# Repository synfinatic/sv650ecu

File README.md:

## Suzuki SV650 ECU Decoder

This is the Arduino code (for a [PJRC Teensy 2.0](http://www.pjrc.com/store/teensy.html)) 
and necessary CAD/schematic files for creating a PCB to creating your own 
2nd Generation SV650 ECU Decoder to replace the error lights & codes normally 
displayed by the stock dash unit.

This supports the following:

 * Oil pressure warning light
 * Neutral light
 * EFI warning light
 * Low fuel light *
 * Display the water temp from the the stock water temp sensor
 * Ability to decode EFI error codes from the SV650 ECU
 * TPS adjustment indicator **

[*] Note: Untested.

[**] Note: Normally the 4 digit LED display shows the water temp. 
To show the TPS indicator or ECU error codes, you’ll need to use a 
“Suzuki diagnostic tool” (aka a paperclip) to short two wires per the shop manual.

More information about this project is available 
[on my blog](http://synfin.net/sv650ecu "Suzuki SV650 ECU Decoder") and 
[on the wiki](https://github.com/synfinatic/sv650ecu/wiki).

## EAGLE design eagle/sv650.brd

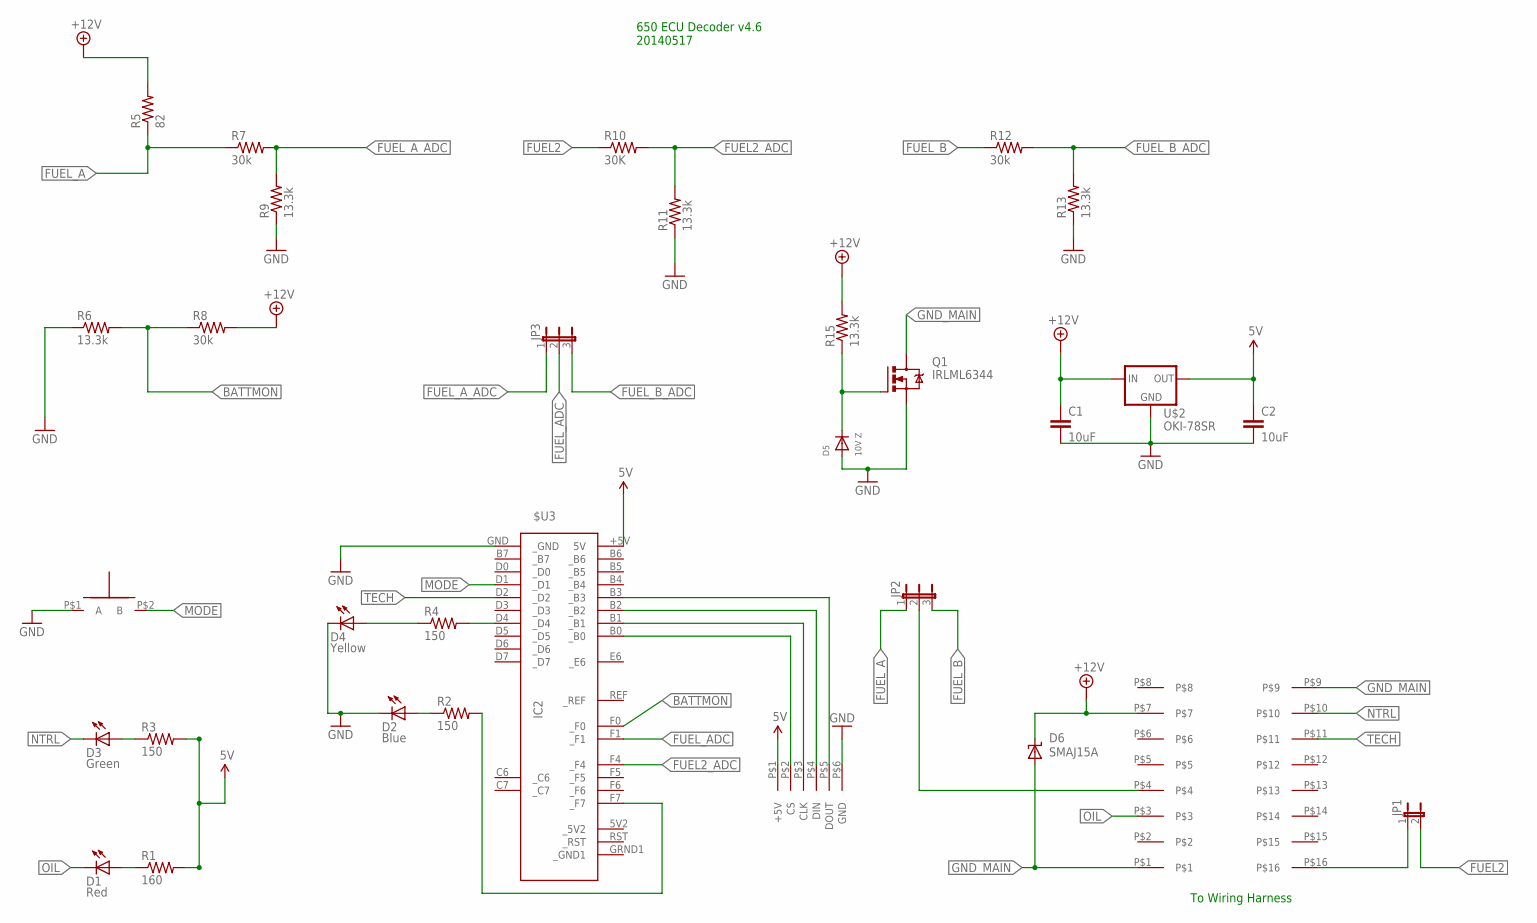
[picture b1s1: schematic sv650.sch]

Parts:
$U3: IC2; TEENSY
C1, C2: 10uF; C0805
D1: Red; LED10MM
D2: Blue; LED5MM
D3: Green; LED10MM
D4: Yellow; LED10MM
D5: 10V Z; SOD-123
D6: SMAJ15A; SMBG
JP1: JP1E; JP1
JP2, JP3: JP2E; JP2
Q1: IRLML6344; SOT23
R1: 160; M0805; MPN CRCW0805160RFKEA
R2, R3, R4: 150; M0805; MPN MCHP05W4F1500T5E
R5: 82; AXIAL-0.9
R6: 13.3k; M0805; MPN CRCW080510K0FKTA
R7, R12: 30k; M0805
R8: 30k; M0805; MPN CRCW080510K0FKTA
R9, R11, R13, R15: 13.3k; M0805
R10: 30K; M0805
U$1: OASIS-7-SEG-DISPLAY
U$2: OKI-78SR; OKI-78SR-H
U$3: TE-174975-2
U$10: R13-509A-05-BB/R13-509A-05-BR

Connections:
5V: $U3.+5V (5V), C2.1, R1.2, R3.2, U$1.P$1 (+5V), U$2.P$3 (OUT)
+12V: C1.1, D6.C, R5.P$2 (2), R8.2, R15.2, U$2.P$1 (IN), U$3.P$7
BATTMON: $U3.F0 (_F0), R6.2, R8.1
FUEL2: JP1.2, R10.1
FUEL2_ADC: $U3.F4 (_F4), R10.2, R11.2
FUEL_A: JP2.1, R5.P$1 (1), R7.1
FUEL_ADC: $U3.F1 (_F1), JP3.2
FUEL_A_ADC: JP3.1, R7.2, R9.2
FUEL_B: JP2.3, R12.1
FUEL_B_ADC: JP3.3, R12.2, R13.2
GND: $U3.GND (_GND), C1.2, C2.2, D2.K (C), D4.K (C), D5.A, Q1.2 (S), R6.1, R9.1, R11.1, R13.1, U$1.P$6 (GND), U$2.P$2 (GND), U$10.P$1 (A)
GND_MAIN: D6.A, Q1.3 (D), U$3.P$1, U$3.P$9
MODE: $U3.D1 (_D1), U$10.P$2 (B)
unnamed: $U3.B0 (_B0), U$1.P$2 (CS)
unnamed: $U3.B1 (_B1), U$1.P$3 (CLK)
unnamed: $U3.B2 (_B2), U$1.P$4 (DIN)
unnamed: $U3.B3 (_B3), U$1.P$5 (DOUT)
unnamed: D3.A, R3.1
unnamed: D2.A, R2.1
unnamed: D1.A, R1.1
unnamed: $U3.D4 (_D4), R4.2
unnamed: JP2.2, U$3.P$4
unnamed: JP1.1, U$3.P$16
unnamed: $U3.F7 (_F7), R2.2
unnamed: D5.C, Q1.1 (G), R15.1
NTRL: D3.K (C), U$3.P$10
OIL: D1.K (C), U$3.P$3
R2: D4.A, R4.1
TECH: $U3.D2 (_D2), U$3.P$11

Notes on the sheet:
To Wiring Harness
650 ECU Decoder v4.6 20140517

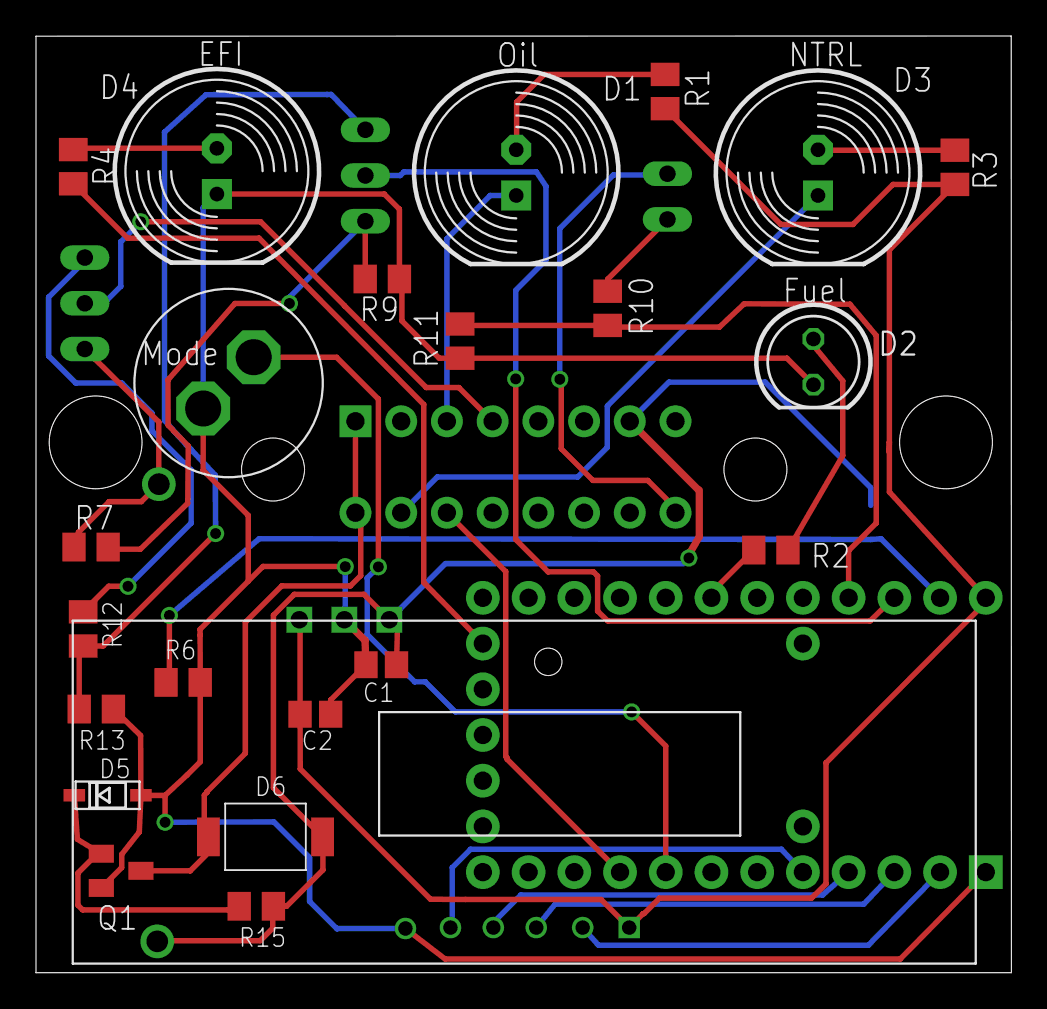
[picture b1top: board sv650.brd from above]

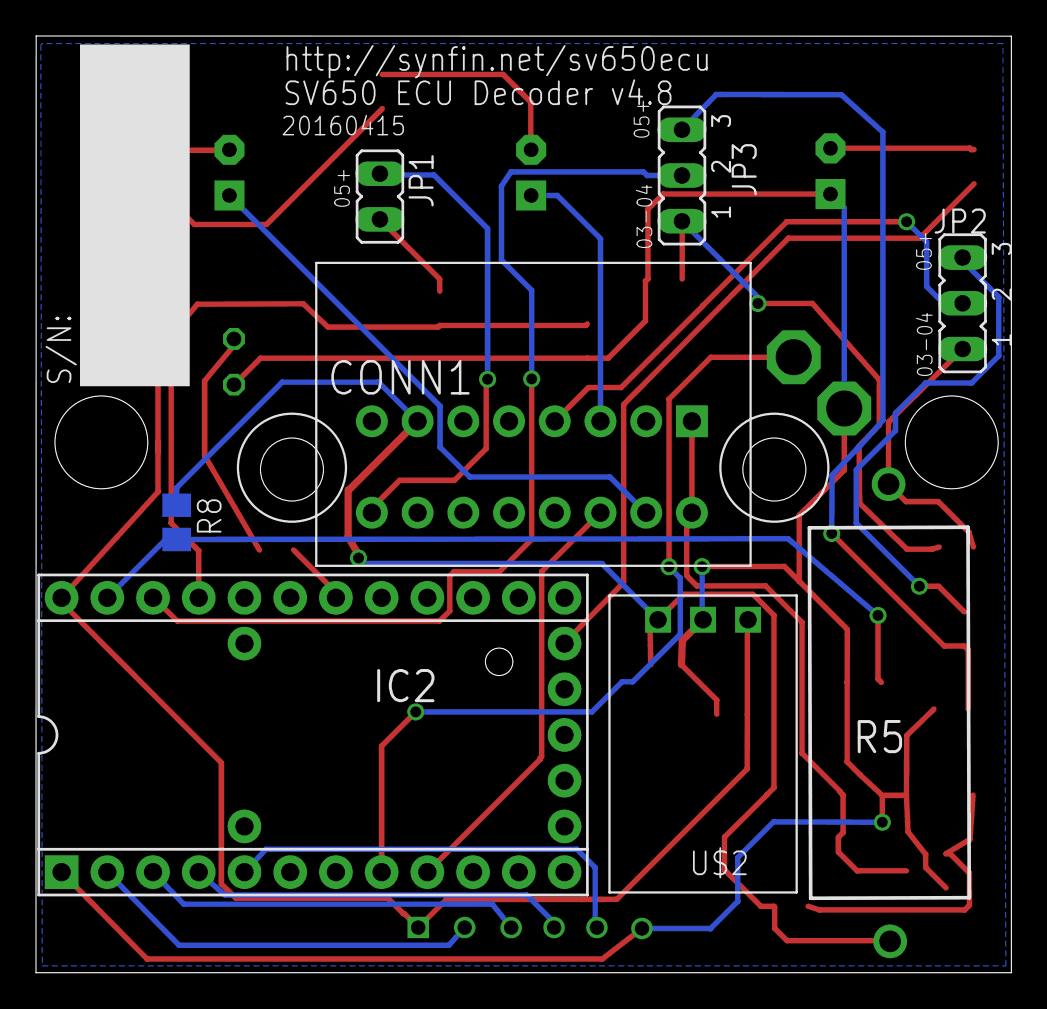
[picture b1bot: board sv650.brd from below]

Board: 2 copper layers, 54.2 x 52.0 mm, 32 parts (8 on the bottom side), 29 nets.

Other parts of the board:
U$5: STANDOFF

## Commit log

2013-09-09 Initial checkin of Teensy 2.0 code and Diptrace files necessary for creating a PCB
2013-09-09 add license & copyright information to the code file
2013-09-09 add Eagle files which are a work in progress!
2013-09-10 add two Arduino tools I used to help develop the code in sv650_reader Neither are particularly pretty/clean, but they are good starting points for creating your own ECU emulator for other Suzuki seri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
2013-09-10 improve board layout and update resistor divider circuit
2013-09-10 add comment to remind people they need to hack SoftwareSerial library to support 7800 baud
2013-09-11 add .gitignore Update schema and board with updated connector, resistors for voltage divider and zener.
2013-09-12 ignore all gerber/drill files
2013-09-12 update layout of 7805 to use a pad for solder not drill hole for hard mounting. Update silkscreen and improve layout for sending to OshPark for fabrication.
    Just waiting on feedback on voltage divider & zener.
2013-09-14 board as ordered from OshPark for v4.0
2013-11-28 reorganize code to be easier to maintain and understand.
2013-11-29 significantly improve code comments and organization further
2013-11-29 document what each Arduino project is for
2013-11-29 explain more about the project and what it does
2013-11-29 remove extra separator
2013-11-30 add important note about 7800 baud
2013-11-30 use bullets
2013-11-30 add support for celcius temp readings more small code clean up
2013-12-14 Move fuel LED down to have bigger gap to neutral light rev board to 4.1 add date code to board top silk
2013-12-27 Fix "LO F" message on LED display Fix bad LED error code due to error == -1 Update copyright to 2014 in preperation for the new year
2013-12-30 update board & schema to v4.1 - Add 5V zener to protect ADC from shorts - Add .1uF cap to even out ADC line from noise - Tweak placement of low fuel LED - Tweak placement of S/N: XXXXXX
2013-12-30 fix S/N: XXXXX so it is not hidden by the wiring harness connector
2013-12-31 modify the position of parts & traces to be a little cleaner move LED's away from the top edge of the board
2013-12-31 remove 20V zener replace 5V zener with 4.7V zener (hard to find 5V zeners) merge 10K + 22K into a single 30K resistor clean up traces & remove lots of vias
2014-01-16 Add 'mode' button Add means to detect Very Low Fuel on later models Move +12V back to ignition
2014-01-16 Add code to measure & display battery/charge voltage Fix bug with display characters Add support for controlling the colon on the LED display
2014-03-10 put BATT_MON (A0) pin into input mode so we can read the battery voltage
    Also prevents feedback loop which will end up damaging the Arduino
    and overheat the LM7805.
2014-03-10 Update to v4.2. - Move via away from LM7805 to prevent shorting - Increase size of S/N space
2014-03-10 update to show v4.2 and date
2014-03-10 add comment about setting BATT_MON pin to INPUT
2014-03-11 update temp every second pick a ZENER_DROP_VOLTAGE which works well for both USB and bike battery
2014-03-11 change mode button to pin D1/6 so we can assign an interrupt to it
2014-04-22 update code to use correct pins and dynamically put unused pins in OUTPUT
2014-04-22 - update board to v4.2 with LM7805 w/ heat sink - fix mode button to use a pin supporting interrupts - remove external pullup resistors
2014-04-22 update board to v4.3 - switch to LM2674-5.0 - Fix 20V schottky diode
2014-04-22 Enable DL1000 error codes
2014-04-23 update comments to clarify these are verified SV1000 codes which might work with DL1000.
2014-04-26 low fuel doesn't work
2014-04-27 Fuel level LED is now controlled by Teensy Use LT082CP to measure fuel sensor add 5W 82ohm resistor to fuel line Remove Fuel2 jumper/support
2014-05-19 Replace LM7805 with new Murata 5V switching module Move EFI from D6 to D4 to avoid interrupt conflict Add ground plane Add N channel MOSFET for reverse battery protection Remove 5.1V zener from batte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
2014-05-19 replace 16V zener with 15V TVS
2014-05-19 update to v4.6 move jumpers to back side of board
2014-05-19 move jumper silk mask descriptions to bsilk
2014-05-19 reroute some traces to be cleaner ordered v4.6 via oshpark
2014-08-04 update code to support v4.2 board design
2014-08-08 add TEMP_WARN to solid light the EFI lamp at 230F
2014-08-09 Fix water temp EFI alarm light
2014-08-21 New firmware for 4.6 board support
    - Adds support for the mode button to cycle modes
    - Adds support for volts
    - Adds support for water temp
    - EFI is
    - solid for EFI error
    - slow flash bad ECU comms
2014-09-07 switch D5 to a SOD-123 package
2014-09-07 Fix battery monitor
    used_pins[] were being put in OUTPUT mode, rather then the opposite.
2015-01-10 update readme to reflect v4.6 board
2015-03-28 First pass at using Nokia LCD display
2015-04-15 don't include eagle files we don't need
2015-04-24 update board to have a 6mm switch on front
2015-04-26 v5.0 board with Nokia 5110 LCD screen
    as ordered from OSHPark
2016-04-07 Add ST6961 library
2016-04-07 Update SV650 Reader to build cleanly under Arduino IDE 1.6.7
    Builds without errors, but I haven't tested the code yet. YMMV!
2016-04-15 Work on v4.8 board
    - Updates power module footprint to make pads bigger so the pins fit
    - Other small tweaks based on feedback??
2017-01-28 add more things we don't care about to gitignore
2018-10-09 Update README.md
    EFI error code reading works great!

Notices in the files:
parts and their libraries:
teensy: Licensed Under Creative Commons Attribution-ShareAlike 3.0 Unported (CC BY-SA 3.0)
SparkFun: Licensing: CC v3.0 Share-Alike You are welcome to use this library for commercial purposes.
